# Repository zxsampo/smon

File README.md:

#./pd2tex    # -*-mode: pd; coding: latin-1;-*-
smon - Embedded Service Monitor
###############################

Embedded service monitor and sensor net firmware and hardware.

Copyright (c) 2020 Sampo Kellomaki (sampo-smon20@zxid.org)
All Rights Reserved.

See file LICENSING for (open source) licensing terms.

 smon
  |
  +-- dok/                 Documentation
  +-- sens-rf-1w-1-kicad/  KiCAD project for the hardware
  `-- smonfw/              smon firmware source code

Toolchains
==========

Hardware was designed uing kicad 5.x

Firmware can be compiled with sdcc

You should use CCLib on Arduino for intial flashing.

--Sampo

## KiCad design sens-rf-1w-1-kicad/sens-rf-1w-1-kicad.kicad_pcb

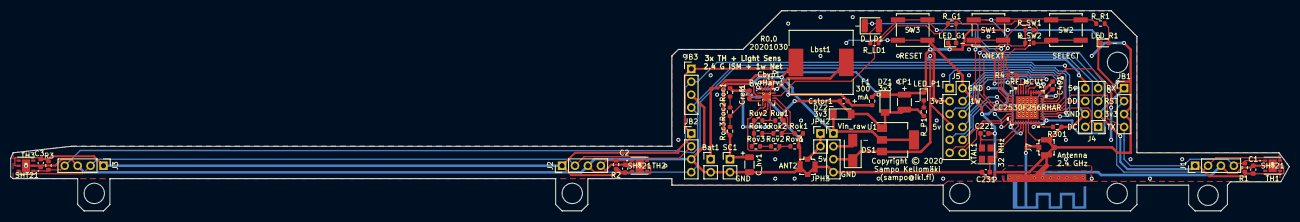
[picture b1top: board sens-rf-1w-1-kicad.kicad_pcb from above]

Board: 2 copper layers, 251.4 x 39.4 mm, 67 parts (1 on the bottom side), 51 nets.

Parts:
ANT1: SWRA117D
ANT2: U.FL; U.FL_Molex_MCRF_73412-0110_Vertical
Bat1: 4v2; PinHeader_1x02_P2.54mm_Vertical
C1, C2, C3: 100n; C_0603_1608Metric
C221, C231: 27p; C_0603_1608Metric
C401: 1u; C_0603_1608Metric
CP1: 100u; C_1210_3225Metric
C_hv1: 4u7; C_1206_3216Metric
Cbyp1: 100n; C_0603_1608Metric
Cref1: 10n; C_0603_1608Metric
Cstor1: 4u7; C_0603_1608Metric
DS1: Schottky; D_SMA
DZ1, DZ2: 3v3; D_MiniMELF
D_LD1: Light detector; D_1210_3225Metric
F1: 300mA polyfuse; R_0603_1608Metric
J1, J2, J3: I2C; PinHeader_1x04_P2.54mm_Vertical
J4: Debug port; PinHeader_2x04_P2.54mm_Vertical
J5: SPI / GPIO; PinHeader_2x06_P2.54mm_Vertical
J7: U.FL; U.FL_Molex_MCRF_73412-0110_Vertical
JB1, JB2, JB3: I2C; PinHeader_1x04_P2.54mm_Vertical
JPH2: Hdr; PinHeader_1x02_P2.54mm_Vertical
JPH3: Hdr; PinHeader_1x04_P2.54mm_Vertical
LED_G1: Green RX; LED_0603_1608Metric
LED_P1: Orange Power; LED_0603_1608Metric
LED_R1: Red TX; LED_0603_1608Metric
Lbst1: 22uH; L_12x12mm_H6mm
PwrHarv1: BQ25504; QFN-16-1EP_3x3mm_P0.5mm_EP1.75x1.75mm_ThermalVias
R1, R2, R3, R4: 10k; R_0603_1608Metric
R301: 56k; R_0603_1608Metric
RF_MCU1: CC2530F256RHAR
R_G1: 220; R_0603_1608Metric
R_LD1: 10k; R_0603_1608Metric
R_P1: 220; R_0603_1608Metric
R_R1: 220; R_0603_1608Metric
R_SW1: 10k; R_0603_1608Metric
R_SW2: 56k; R_0603_1608Metric
Roc1: 10M; R_0603_1608Metric
Roc2: 5M1; R_0603_1608Metric
Roc3: 4M7; R_0603_1608Metric
Rok1, Rok2: 5M1; R_0603_1608Metric
Rok3: 1M; R_0603_1608Metric
Rov1: 5M1; R_0603_1608Metric
Rov2: 2M2; R_0603_1608Metric
Rov3: 1M5; R_0603_1608Metric
Ruv1: 4M7; R_0603_1608Metric
Ruv2: 5M1; R_0603_1608Metric
SC1: 0v6; PinHeader_1x02_P2.54mm_Vertical
SW1: Next; SW_Push_1P1T_NO_CK_KSC6xxJ
SW2: Select; SW_Push_1P1T_NO_CK_KSC6xxJ
SW3: Reset; SW_Push_1P1T_NO_CK_KSC6xxJ
TH1, TH2, TH3: SHT21
U1: AMS1117-3.3; SOT-223-3_TabPin2
XTAL1: 32MHz; Crystal_SMD_3225-4Pin_3.2x2.5mm

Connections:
+3V3: C1.1, C2.1, C3.1, CP1.1, DZ1.1, F1.1, J1.1, J2.1, J3.1, J4.3, J5.3, JB1.1, JB2.1, JB3.1, LED_G1.1, LED_P1.1, LED_R1.1, R1.1, R2.1, R3.1, R4.1, RF_MCU1.10, RF_MCU1.21, RF_MCU1.24, RF_MCU1.27, RF_MCU1.28, RF_MCU1.29, RF_MCU1.31, RF_MCU1.39, TH1.5, TH2.5, TH3.5
+5V: DS1.1, J4.8, J5.7, JPH3.3, U1.3
/ANT_P: ANT1.1, J7.1, RF_MCU1.25
/BYP1v8: C401.2, RF_MCU1.40
/CLK: J5.6, RF_MCU1.5
/DEBUG_CLK: J4.2, RF_MCU1.34
/DEBUG_DATA: J4.6, RF_MCU1.35
/I2C-SCL: J1.2, J2.2, J3.2, JB1.2, JB2.2, JB3.2, R4.2, RF_MCU1.8, TH1.6, TH2.6, TH3.6
/I2C-SDA1: J1.4, JB1.4, R1.2, RF_MCU1.36, TH1.1
/I2C-SDA2: J2.4, JB2.4, R2.2, RF_MCU1.33, TH2.1
/I2C-SDA3: J3.4, JB3.4, R3.2, RF_MCU1.32, TH3.1
/KEYSN: RF_MCU1.13, R_SW1.1, R_SW2.1
/LDET: D_LD1.1, RF_MCU1.12
/LED_G_AN: RF_MCU1.9, R_G1.1, R_LD1.1
/LED_R_AN: RF_MCU1.11, R_R1.1, SW1.1, SW2.1
/MISO: J5.1, RF_MCU1.37
/MOSI: J5.4, RF_MCU1.38
/P0_0: J5.12, RF_MCU1.19
/P0_1: J5.11, RF_MCU1.18
/P0_4: J5.10, RF_MCU1.15
/P0_5: J5.9, RF_MCU1.14
/P1_3: J5.8, RF_MCU1.7
/Power/OC: PwrHarv1.3, Roc2.1, Roc3.2
/Power/OKH: PwrHarv1.9, Rok2.1, Rok3.2
/Power/OKP: PwrHarv1.10, Rok1.1, Rok2.2
/Power/OV: PwrHarv1.6, Rov1.1, Rov2.2
/Power/UV: PwrHarv1.8, Ruv1.1, Ruv2.2
/Power/Vbat: Bat1.1, PwrHarv1.14
/Power/Vin_raw: C_hv1.1, DZ2.1, JPH3.1, Lbst1.1, PwrHarv1.2, Roc3.1, SC1.1, U1.2
/Power/pwr_3v3: Cbyp1.1, Cstor1.1, F1.2, PwrHarv1.15
/RST_N: J4.5, PwrHarv1.11, RF_MCU1.20, SW3.1
/RX: J4.7, RF_MCU1.17
/SS1: J5.5, RF_MCU1.6
/TX: J4.1, RF_MCU1.16
/XTAL1: C221.1, RF_MCU1.22, XTAL1.3
/XTAL2: C231.1, RF_MCU1.23, XTAL1.1
GNDD: ANT1.2, ANT2.2, Bat1.2, C1.2, C2.2, C3.2, C221.2, C231.2, C401.1, CP1.2, C_hv1.2, Cbyp1.2, Cref1.2, Cstor1.2, DZ1.2, DZ2.2, J1.3, J2.3, J3.3, J4.4, J5.2, J7.2, JB1.3, JB2.3, JB3.3, JPH3.4, PwrHarv1.1, PwrHarv1.5, PwrHarv1.12, PwrHarv1.13, PwrHarv1.17, R301.1, RF_MCU1.1, RF_MCU1.2, RF_MCU1.3, RF_MCU1.4, RF_MCU1.26, RF_MCU1.41, R_P1.1, Roc1.2, Rok1.2, Rov1.2, Ruv1.2, SC1.2, SW3.2, TH1.2, TH1.7, TH2.2, TH2.7, TH3.2, TH3.7, U1.1
unnamed: ANT2.1, JPH2.1, JPH2.2
unnamed: Cref1.1, PwrHarv1.4
unnamed: DS1.2, JPH3.2
unnamed: D_LD1.2, R_LD1.2
unnamed: LED_G1.2, R_G1.2
unnamed: LED_P1.2, R_P1.2
unnamed: LED_R1.2, R_R1.2
unnamed: Lbst1.2, PwrHarv1.16
unnamed: PwrHarv1.7, Rok3.1, Rov3.1, Ruv2.1
unnamed: R301.2, RF_MCU1.30
unnamed: R_SW1.2, SW1.2
unnamed: R_SW2.2, SW2.2
unnamed: Roc1.1, Roc2.2
unnamed: Rov2.1, Rov3.2

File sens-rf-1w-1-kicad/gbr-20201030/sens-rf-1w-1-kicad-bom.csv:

"Id";"Designator";"Package";"Quantity";"Designation";"Supplier and ref";
1;"DS1";"D_SMA";1;"Schottky";;;
2;"F1";"R_0603_1608Metric";1;"300mA polyfuse";;;
3;"JPH3";"PinHeader_1x04_P2.54mm_Vertical";1;"Hdr";;;
4;"JPH2";"PinHeader_1x02_P2.54mm_Vertical";1;"Hdr";;;
5;"DZ2,DZ1";"D_MiniMELF";2;"3v3";;;
6;"ANT2,J7";"U.FL_Molex_MCRF_73412-0110_Vertical";2;"U.FL";;;
7;"J4";"PinHeader_2x04_P2.54mm_Vertical";1;"Debug port";;;
8;"JB1,J1,JB3,JB2,J3,J2";"PinHeader_1x04_P2.54mm_Vertical";6;"I2C";;;
9;"U1";"SOT-223-3_TabPin2";1;"AMS1117-3.3";;;
10;"ANT1";"SWRA117D";1;"SWRA117D";;;
11;"PwrHarv1";"QFN-16-1EP_3x3mm_P0.5mm_EP1.75x1.75mm_ThermalVias";1;"BQ25504";;;
12;"TH3,TH2,TH1";"SHT21";3;"SHT21";;;
13;"RF_MCU1";"CC2530F256RHAR";1;"CC2530F256RHAR";;;
14;"XTAL1";"Crystal_SMD_3225-4Pin_3.2x2.5mm";1;"32MHz";;;
15;"SW3";"SW_Push_1P1T_NO_CK_KSC6xxJ";1;"Reset";;;
16;"SW2";"SW_Push_1P1T_NO_CK_KSC6xxJ";1;"Select";;;
17;"SW1";"SW_Push_1P1T_NO_CK_KSC6xxJ";1;"Next";;;
18;"SC1";"PinHeader_1x02_P2.54mm_Vertical";1;"0v6";;;
19;"Ruv2,Rov1,Rok2,Rok1,Roc2";"R_0603_1608Metric";5;"5M1";;;
20;"Ruv1,Roc3";"R_0603_1608Metric";2;"4M7";;;
21;"Rov3";"R_0603_1608Metric";1;"1M5";;;
22;"Rov2";"R_0603_1608Metric";1;"2M2";;;
23;"Rok3";"R_0603_1608Metric";1;"1M";;;
24;"Roc1";"R_0603_1608Metric";1;"10M";;;
25;"R_SW2,R301";"R_0603_1608Metric";2;"56k";;;
26;"R_SW1,R_LD1,R4,R3,R2,R1";"R_0603_1608Metric";6;"10k";;;
27;"R_R1,R_P1,R_G1";"R_0603_1608Metric";3;"220";;;
28;"LED_R1";"LED_0603_1608Metric";1;"Red TX";;;
29;"LED_P1";"LED_0603_1608Metric";1;"Orange Power";;;
30;"LED_G1";"LED_0603_1608Metric";1;"Green RX";;;
31;"Lbst1";"L_12x12mm_H6mm";1;"22uH";;;
32;"J5";"PinHeader_2x06_P2.54mm_Vertical";1;"SPI / GPIO";;;
33;"D_LD1";"D_1210_3225Metric";1;"Light detector";;;
34;"Cstor1";"C_0603_1608Metric";1;"4u7";;;
35;"Cref1";"C_0603_1608Metric";1;"10n";;;
36;"CP1";"C_1210_3225Metric";1;"100u";;;
37;"C_hv1";"C_1206_3216Metric";1;"4u7";;;
38;"Cbyp1,C3,C2,C1";"C_0603_1608Metric";4;"100n";;;
39;"C401";"C_0603_1608Metric";1;"1u";;;
40;"C231,C221";"C_0603_1608Metric";2;"27p";;;
41;"Bat1";"PinHeader_1x02_P2.54mm_Vertical";1;"4v2";;;

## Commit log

2020-11-09 Populate
2020-11-09 Founding
2020-11-11 boot order, led blink
2020-11-11 document more I/O pins
2020-11-19 First cut at the Makefile
2020-11-19 boot compiles
2020-11-19 Compiles, but not much control over output

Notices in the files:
sens-rf-1w-1-kicad/sens-rf-1w-1-kicad.kicad_pcb:
Copyright © 2020
parts and their libraries:
Copyright 2016 Accelerated Designs. All rights reserved.
